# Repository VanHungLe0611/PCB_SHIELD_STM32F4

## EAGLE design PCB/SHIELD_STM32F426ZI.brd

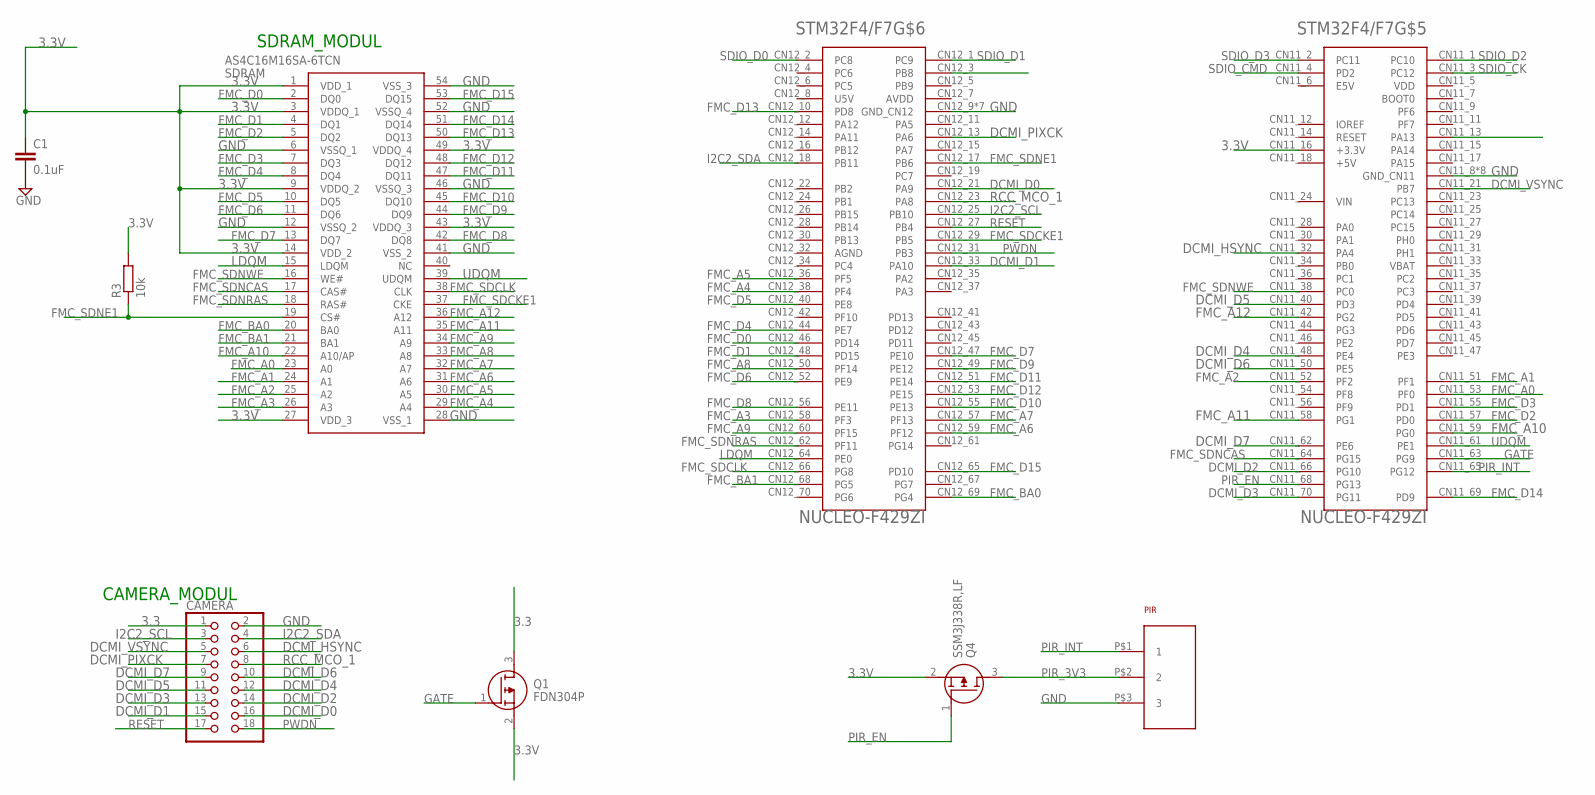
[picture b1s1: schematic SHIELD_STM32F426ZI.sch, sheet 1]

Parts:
C1: 0.1uF; C0402K
CAMERA: 0; 2X09
PIR: SENBA_PIR_3PIN; SENBA_PIR
Q1: FDN304P; SOT95P237X112-3N
Q4: SSM3J338R,LF; SSM3J332RLFT
R3: 10k; C0402K
SDRAM: AS4C16M16SA-6TCN; SOP80P1176X120-54N
STM32F4/F7: NUCLEO-F429ZI; MODULE_NUCLEO-F429ZI

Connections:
3.3: CAMERA.1, Q1.3 (D)
3.3V: C1.1, Q1.2 (S), Q4.2 (S), R3.2, SDRAM.1 (VDD_1), SDRAM.3 (VDDQ_1), SDRAM.9 (VDDQ_2), SDRAM.14 (VDD_2), SDRAM.27 (VDD_3), SDRAM.43 (VDDQ_3), SDRAM.49 (VDDQ_4), STM32F4/F7.CN11_16 (+3.3V); also elsewhere on the board
CARD_DET: STM32F4/F7.CN12_3 (PB8); also elsewhere on the board
DCMI_D0: CAMERA.16, STM32F4/F7.CN12_21 (PA9)
DCMI_D1: CAMERA.15, STM32F4/F7.CN12_33 (PA10)
DCMI_D2: CAMERA.14, STM32F4/F7.CN11_66 (PG10)
DCMI_D3: CAMERA.13, STM32F4/F7.CN11_70 (PG11)
DCMI_D4: CAMERA.12, STM32F4/F7.CN11_48 (PE4)
DCMI_D5: CAMERA.11, STM32F4/F7.CN11_40 (PD3)
DCMI_D6: CAMERA.10, STM32F4/F7.CN11_50 (PE5)
DCMI_D7: CAMERA.9, STM32F4/F7.CN11_62 (PE6)
DCMI_HSYNC: CAMERA.6, STM32F4/F7.CN11_32 (PA4)
DCMI_PIXCK: CAMERA.7, STM32F4/F7.CN12_13 (PA6)
DCMI_VSYNC: CAMERA.5, STM32F4/F7.CN11_21 (PB7)
FMC_A0: SDRAM.23 (A0), STM32F4/F7.CN11_53 (PF0)
FMC_A1: SDRAM.24 (A1), STM32F4/F7.CN11_51 (PF1)
FMC_A2: SDRAM.25 (A2), STM32F4/F7.CN11_52 (PF2)
FMC_A3: SDRAM.26 (A3), STM32F4/F7.CN12_58 (PF3)
FMC_A4: SDRAM.29 (A4), STM32F4/F7.CN12_38 (PF4)
FMC_A5: SDRAM.30 (A5), STM32F4/F7.CN12_36 (PF5)
FMC_A6: SDRAM.31 (A6), STM32F4/F7.CN12_59 (PF12)
FMC_A7: SDRAM.32 (A7), STM32F4/F7.CN12_57 (PF13)
FMC_A8: SDRAM.33 (A8), STM32F4/F7.CN12_50 (PF14)
FMC_A9: SDRAM.34 (A9), STM32F4/F7.CN12_60 (PF15)
FMC_A10: SDRAM.22 (A10/AP), STM32F4/F7.CN11_59 (PG0)
FMC_A11: SDRAM.35 (A11), STM32F4/F7.CN11_58 (PG1)
FMC_A12: SDRAM.36 (A12), STM32F4/F7.CN11_42 (PG2)
FMC_BA0: SDRAM.20 (BA0), STM32F4/F7.CN12_69 (PG4)
FMC_BA1: SDRAM.21 (BA1), STM32F4/F7.CN12_68 (PG5)
FMC_D0: SDRAM.2 (DQ0), STM32F4/F7.CN12_46 (PD14)
FMC_D1: SDRAM.4 (DQ1), STM32F4/F7.CN12_48 (PD15)
FMC_D2: SDRAM.5 (DQ2), STM32F4/F7.CN11_57 (PD0)
FMC_D3: SDRAM.7 (DQ3), STM32F4/F7.CN11_55 (PD1)
FMC_D4: SDRAM.8 (DQ4), STM32F4/F7.CN12_44 (PE7)
FMC_D5: SDRAM.10 (DQ5), STM32F4/F7.CN12_40 (PE8)
FMC_D6: SDRAM.11 (DQ6), STM32F4/F7.CN12_52 (PE9)
FMC_D7: SDRAM.13 (DQ7), STM32F4/F7.CN12_47 (PE10)
FMC_D8: SDRAM.42 (DQ8), STM32F4/F7.CN12_56 (PE11)
FMC_D9: SDRAM.44 (DQ9), STM32F4/F7.CN12_49 (PE12)
FMC_D10: SDRAM.45 (DQ10), STM32F4/F7.CN12_55 (PE13)
FMC_D11: SDRAM.47 (DQ11), STM32F4/F7.CN12_51 (PE14)
FMC_D12: SDRAM.48 (DQ12), STM32F4/F7.CN12_53 (PE15)
FMC_D13: SDRAM.50 (DQ13), STM32F4/F7.CN12_10 (PD8)
FMC_D14: SDRAM.51 (DQ14), STM32F4/F7.CN11_69 (PD9)
FMC_D15: SDRAM.53 (DQ15), STM32F4/F7.CN12_65 (PD10)
FMC_SDCKE1: SDRAM.37 (CKE), STM32F4/F7.CN12_29 (PB5)
FMC_SDCLK: SDRAM.38 (CLK), STM32F4/F7.CN12_66 (PG8)
FMC_SDNCAS: SDRAM.17 (CAS#), STM32F4/F7.CN11_64 (PG15)
FMC_SDNE1: R3.1, SDRAM.19 (CS#), STM32F4/F7.CN12_17 (PB6)
FMC_SDNRAS: SDRAM.18 (RAS#), STM32F4/F7.CN12_62 (PF11)
FMC_SDNWE: SDRAM.16 (WE#), STM32F4/F7.CN11_38 (PC0)
GATE: Q1.1 (G), STM32F4/F7.CN11_63 (PG9)
GND: C1.2, CAMERA.2, PIR.P$3 (3), SDRAM.6 (VSSQ_1), SDRAM.12 (VSSQ_2), SDRAM.28 (VSS_1), SDRAM.41 (VSS_2), SDRAM.46 (VSSQ_3), SDRAM.52 (VSSQ_4), SDRAM.54 (VSS_3), STM32F4/F7.CN11_8 (GND_CN11), STM32F4/F7.CN11_19 (GND_CN11), STM32F4/F7.CN11_20 (GND_CN11), STM32F4/F7.CN11_22 (GND_CN11), STM32F4/F7.CN11_49 (GND_CN11), STM32F4/F7.CN11_60 (GND_CN11), STM32F4/F7.CN11_71 (GND_CN11), STM32F4/F7.CN11_72 (GND_CN11), STM32F4/F7.CN12_9 (GND_CN12), STM32F4/F7.CN12_20 (GND_CN12), STM32F4/F7.CN12_39 (GND_CN12), STM32F4/F7.CN12_54 (GND_CN12), STM32F4/F7.CN12_63 (GND_CN12), STM32F4/F7.CN12_71 (GND_CN12), STM32F4/F7.CN12_72 (GND_CN12); also elsewhere on the board
I2C2_SCL: CAMERA.3, STM32F4/F7.CN12_25 (PB10); also elsewhere on the board
I2C2_SDA: CAMERA.4, STM32F4/F7.CN12_18 (PB11); also elsewhere on the board
LDQM: SDRAM.15 (LDQM), STM32F4/F7.CN12_64 (PE0)
MOSFET_SDCARD: STM32F4/F7.CN11_13 (PA13); also elsewhere on the board
PIR_3V3: PIR.P$2 (2), Q4.3 (D)
PIR_EN: Q4.1 (G), STM32F4/F7.CN11_68 (PG13)
PIR_INT: PIR.P$1 (1), STM32F4/F7.CN11_65 (PG12)
PWDN: CAMERA.18, STM32F4/F7.CN12_31 (PB3)
RCC_MCO_1: CAMERA.8, STM32F4/F7.CN12_23 (PA8)
RESET: CAMERA.17, STM32F4/F7.CN12_27 (PB4)
SDIO_CK: STM32F4/F7.CN11_3 (PC12); also elsewhere on the board
SDIO_CMD: STM32F4/F7.CN11_4 (PD2); also elsewhere on the board
SDIO_D0: STM32F4/F7.CN12_2 (PC8); also elsewhere on the board
SDIO_D1: STM32F4/F7.CN12_1 (PC9); also elsewhere on the board
SDIO_D2: STM32F4/F7.CN11_1 (PC10); also elsewhere on the board
SDIO_D3: STM32F4/F7.CN11_2 (PC11); also elsewhere on the board
UDQM: SDRAM.39 (UDQM), STM32F4/F7.CN11_61 (PE1)

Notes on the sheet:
SDRAM_MODUL
CAMERA_MODUL

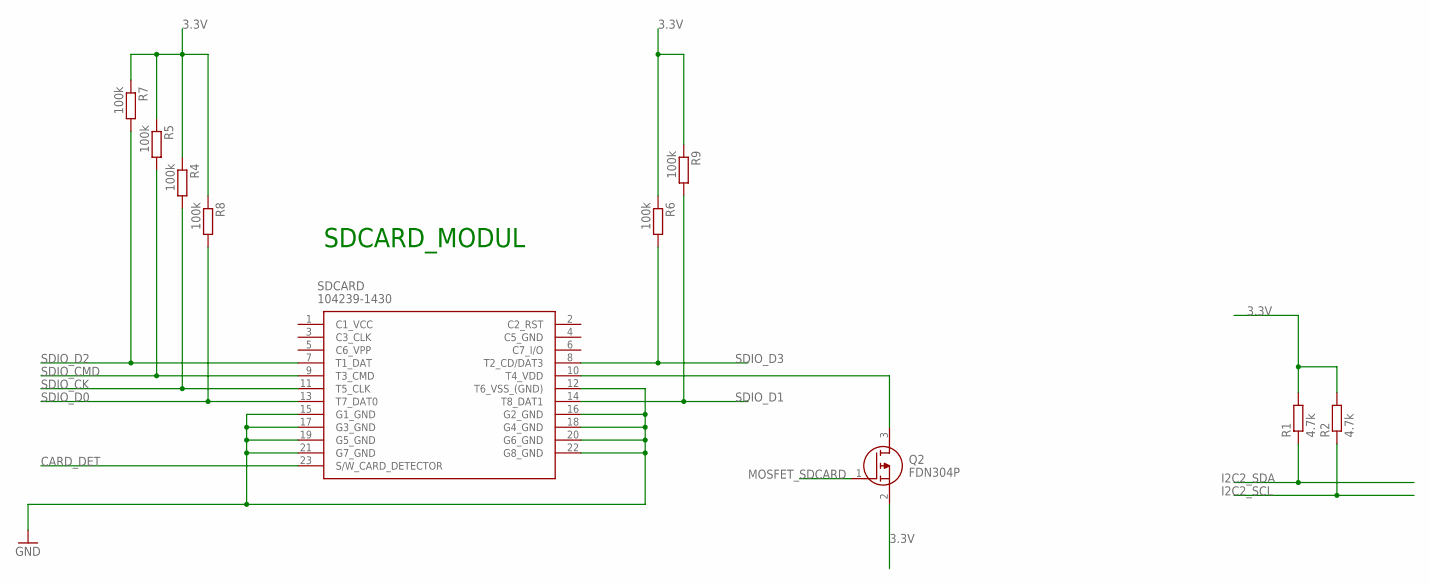
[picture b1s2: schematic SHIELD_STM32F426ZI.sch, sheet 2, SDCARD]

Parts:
Q2: FDN304P; SOT95P237X112-3N
R1, R2: 4.7k; C0402K
R4, R5, R6, R7, R8, R9: 100k; R0402
SDCARD: 104239-1430; 1042391430

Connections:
3.3V: Q2.2 (S), R1.2, R2.2, R4.1, R5.1, R6.1, R7.1, R8.1, R9.1; also elsewhere on the board
CARD_DET: SDCARD.23 (S/W_CARD_DETECTOR); also elsewhere on the board
GND: SDCARD.12 (T6_VSS_(GND)), SDCARD.15 (G1_GND), SDCARD.16 (G2_GND), SDCARD.17 (G3_GND), SDCARD.18 (G4_GND), SDCARD.19 (G5_GND), SDCARD.20 (G6_GND), SDCARD.21 (G7_GND), SDCARD.22 (G8_GND); also elsewhere on the board
I2C2_SCL: R2.1; also elsewhere on the board
I2C2_SDA: R1.1; also elsewhere on the board
MOSFET_SDCARD: Q2.1 (G); also elsewhere on the board
unnamed: Q2.3 (D), SDCARD.10 (T4_VDD)
SDIO_CK: R4.2, SDCARD.11 (T5_CLK); also elsewhere on the board
SDIO_CMD: R5.2, SDCARD.9 (T3_CMD); also elsewhere on the board
SDIO_D0: R8.2, SDCARD.13 (T7_DAT0); also elsewhere on the board
SDIO_D1: R9.2, SDCARD.14 (T8_DAT1); also elsewhere on the board
SDIO_D2: R7.2, SDCARD.7 (T1_DAT); also elsewhere on the board
SDIO_D3: R6.2, SDCARD.8 (T2_CD/DAT3); also elsewhere on the board

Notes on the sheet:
SDCARD_MODUL

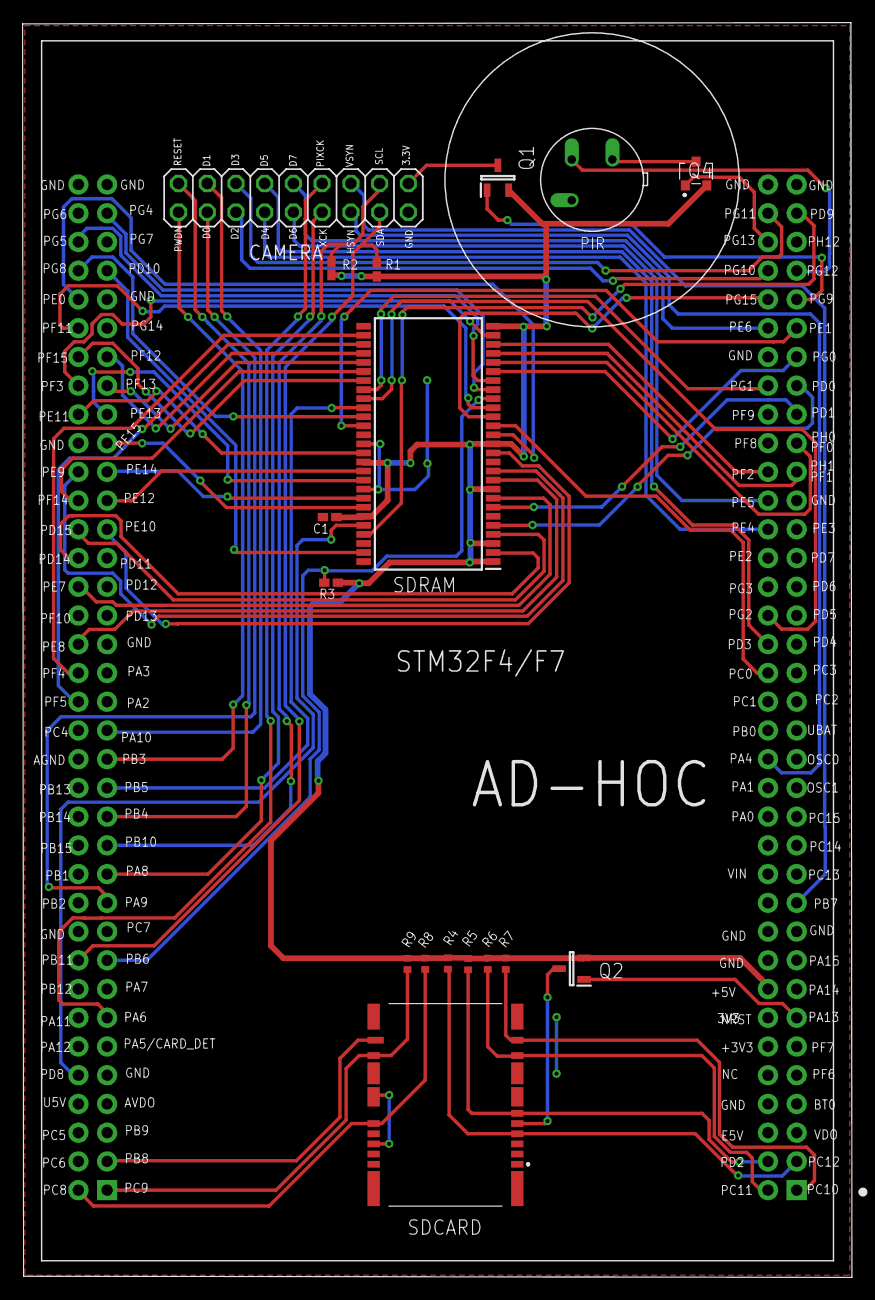
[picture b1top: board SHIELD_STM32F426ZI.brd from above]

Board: 2 copper layers, 73.3 x 110.9 mm, 18 parts (0 on the bottom side), 71 nets.

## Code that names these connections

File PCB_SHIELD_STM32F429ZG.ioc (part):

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Mcu.Name=STM32F429ZITx
Mcu.Package=LQFP144
Mcu.UserName=STM32F429ZITx
PA10.Mode=Slave_8_bits_External_Synchro
PA10.Signal=DCMI_D1
PA13.GPIOParameters=GPIO_Label
PA13.GPIO_Label=MOSFET_SDCARD
PA13.Signal=GPIO_Analog
PA4.Mode=Slave_8_bits_External_Synchro
PA4.Signal=DCMI_HSYNC
PA6.Mode=Slave_8_bits_External_Synchro
PA6.Signal=DCMI_PIXCK
PA8.Mode=Clock-out-1
PA8.Signal=RCC_MCO_1
PA9.Mode=Slave_8_bits_External_Synchro
PA9.Signal=DCMI_D0
PB10.Mode=I2C
PB10.Signal=I2C2_SCL
PB11.Mode=I2C
PB11.Signal=I2C2_SDA
PB5.Mode=SdramChipSelect2_1
PB5.Signal=FMC_SDCKE1
PB6.Mode=SdramChipSelect2_1
PB6.Signal=FMC_SDNE1
PB7.Mode=Slave_8_bits_External_Synchro
PB7.Signal=DCMI_VSYNC
PB8.GPIOParameters=GPIO_Label
PB8.GPIO_Label=CARD_DET
PB8.Signal=GPIO_Output
PC0.Signal=FMC_SDNWE
PC10.Mode=SD_4_bits_Wide_bus
PC10.Signal=SDIO_D2
PC11.Mode=SD_4_bits_Wide_bus
PC11.Signal=SDIO_D3
PC12.Mode=SD_4_bits_Wide_bus
PC12.Signal=SDIO_CK
PC8.Mode=SD_4_bits_Wide_bus
PC8.Signal=SDIO_D0
PC9.Mode=SD_4_bits_Wide_bus
PC9.Signal=SDIO_D1
PD0.Signal=FMC_D2_DA2
PD1.Signal=FMC_D3_DA3
PD10.Signal=FMC_D15_DA15
PD14.Signal=FMC_D0_DA0
PD15.Signal=FMC_D1_DA1
PD2.Mode=SD_4_bits_Wide_bus
PD2.Signal=SDIO_CMD
PD3.Mode=Slave_8_bits_External_Synchro
PD3.Signal=DCMI_D5
PD8.Signal=FMC_D13_DA13
PD9.Signal=FMC_D14_DA14
PE0.Signal=FMC_NBL0
PE1.Signal=FMC_NBL1
PE10.Signal=FMC_D7_DA7
PE11.Signal=FMC_D8_DA8
PE12.Signal=FMC_D9_DA9
PE13.Signal=FMC_D10_DA10
PE14.Signal=FMC_D11_DA11
PE15.Signal=FMC_D12_DA12
PE4.Mode=Slave_8_bits_External_Synchro
PE4.Signal=DCMI_D4
PE5.Mode=Slave_8_bits_External_Synchro
PE5.Signal=DCMI_D6
PE6.Mode=Slave_8_bits_External_Synchro
PE6.Signal=DCMI_D7
PE7.Signal=FMC_D4_DA4
PE8.Signal=FMC_D5_DA5
PE9.Signal=FMC_D6_DA6
PF0.Signal=FMC_A0
PF1.Signal=FMC_A1
PF11.Signal=FMC_SDNRAS
PF12.Signal=FMC_A6
PF13.Signal=FMC_A7
PF14.Signal=FMC_A8
PF15.Signal=FMC_A9
PF2.Signal=FMC_A2
PF3.Signal=FMC_A3
PF4.Signal=FMC_A4
PF5.Signal=FMC_A5
PG0.Signal=FMC_A10
PG1.Signal=FMC_A11
PG10.Mode=Slave_8_bits_External_Synchro
PG10.Signal=DCMI_D2
PG11.Mode=Slave_8_bits_External_Synchro
PG11.Signal=DCMI_D3
PG12.GPIOParameters=GPIO_Label
PG12.GPIO_Label=PIR_IN
PG12.Signal=GPIO_Input
PG13.GPIOParameters=GPIO_Label
PG13.GPIO_Label=MOSFET_PIR
PG13.Signal=GPIO_Output
PG15.Signal=FMC_SDNCAS
PG2.Signal=FMC_A12
PG4.Signal=FMC_A14_BA0
PG5.Signal=FMC_A15_BA1
PG8.Signal=FMC_SDCLK
PG9.GPIOParameters=GPIO_Label
PG9.GPIO_Label=MOSFET_CAMERA
PG9.Signal=GPIO_Output
RCC.HSE_VALUE=8000000
RCC.SYSCLKFreq_VALUE=50000000
RCC.SYSCLKSource=RCC_SYSCLKSOURCE_PLLCLK
RCC.SYSCLKSourceVirtual=RCC_SYSCLKSOURCE_PLLCLK
board=NUCLEO-F429ZI
boardIOC=true

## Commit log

2019-10-11 pcb shield stm32f4
2019-10-11 new raw
2019-10-11 new fmc pin
2019-10-14 sdram und stm32f4 verdrahten
2019-10-14 new with sdramm and sdcard
2019-10-18 neuste vision
2019-10-18 sdcard wird hinzugefügt
2019-10-18 neuster Stand
2019-10-21 modyfi gnd and Ratsnest
2019-10-21 modyfi fault by ERC and DRC
2019-10-25 PCB wurde mit kurzer Leitung korrigiert
2019-10-28 Namen der Elementen und Pin hinzufügen
2019-10-28 Namen der DCMI-Pins hinzufügen und Position des Kondensators korrigieren
2019-10-28 new update
2019-10-28 new layout update
2019-11-08 add mosfet and fix GPIOs for sdram and sdcard
2019-11-11 new position camrera and pir sensor
2019-11-11 new position camera and add pir sensor
2019-11-15 fix route
2019-11-15 fix route 1
2019-11-18 new route 2
2019-11-18 new route 3
